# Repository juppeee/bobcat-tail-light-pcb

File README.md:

# Tail Light PCB for the AN3DRC Skid Steer Loader

PCB for working tail, brake and reverse lights in the tailgate of the
AN3DRC 3D-printed RC Tracked Skid Steer Loader.

> **The skid steer loader is not my design.** The original model, including the tailgate and
> the light module sketch, is by **Andrew (AN3DRC)**. You need his model to build this:
> **[buy it on Cults3D](https://cults3d.com/de/modell-3d/spiel/3d-printed-rc-tracked-skid-steer-loader-in-1-8-5-scale-by-an3drc-an3drc_construction)**.
> This repo only adds the tail light PCB.

> [!TIP]
> **Where to get the board:** I ordered mine from **[JLCPCB](https://jlcpcb.com)**. It worked
> very well and wasn't expensive. Upload the Gerber ZIP from the
> [release](../../releases/latest) and keep the default settings, that's it.
> Any other PCB maker works too, see [How to order](#how-to-order).

**Print files (tailgate frame, bezel, LED housings, lenses) and assembly: [MakerWorld](https://makerworld.com/de/collections/37654355-bobcat-an3drc-skid-steer)**

**[View the assembled PCB in 3D](3D/Tail_Light_PCB_THT.stl)** (GitHub shows an interactive viewer: rotate, zoom)

Board: 134 × 30 mm, 2 layers, 1.6 mm. 8 LEDs (3 mm) on the front facing the tailgate, all
other parts on the back. 4 mounting holes 2.2 mm (M2 or 2.2 mm self-tapping screws, max. 5 mm long).
Driven by a Pro Micro: 4 channels, each pin HIGH switches its two LEDs on through a low-side
MOSFET. The LEDs run from the 12 V battery (3S LiPo).

## Download

Ready-to-upload Gerber ZIPs are attached to the [latest release](../../releases/latest).

## How to order

Any PCB maker works (JLCPCB, PCBWay, Aisler, Elecrow, ...). Pick the one you like, prices
differ more by shipping than by the board.

**1. Board only (THT or SMD version)**
1. Download the Gerber ZIP of your version from the [release](../../releases/latest):
   `Heck_LED_THT_Gerber.zip` or `Heck_LED_SMD_Gerber.zip`.
2. Upload the ZIP **as it is**. Don't unpack it, the maker reads the outline, size and layers from it.
3. Settings: keep the defaults. If asked:

   | Option | Value |
   |---|---|
   | Layers | 2 |
   | Thickness | 1.6 mm |
   | Material | FR-4 |
   | Copper | 1 oz |
   | Surface finish | HASL (lead-free if you prefer), ENIG also fine |
   | Solder mask / silkscreen color | any |
   | Quantity | the minimum (usually 5), one board per tailgate |

   Some makers print an order number on the board. You can usually remove it for a small fee or leave it, it's on the back.
4. Solder the parts yourself (see [Parts per tailgate](#parts-per-tailgate) and `BOM.csv`).

**2. Board with SMD parts already assembled (SMD version only)**

Order like above, then switch on the maker's assembly service ("PCB Assembly", "SMT", ...) and upload two more files from `2_SMD_factory_assembled`:

| File | What the maker calls it |
|---|---|
| `JLCPCB_BOM.csv` | BOM / bill of materials. Columns: value, designators, footprint, LCSC part number |
| `JLCPCB_CPL.csv` (JLCPCB) or `pick_and_place_generic.csv` (others) | CPL / centroid / pick and place / position file |

- Assembly side: **Bottom**. All SMD parts sit on the back, the LEDs are on the front.
- In the preview, check that the four SOT-23 MOSFETs (Q1–Q4) sit with their three pins on the three pads. If they're rotated, turn them in the preview tool.
- The LCSC numbers match JLCPCB's parts library. With other makers, use them to look up the part (value + package is all that matters: 0603 resistors 1 %, 2N7002 in SOT-23).
- Afterwards you still solder the 8 LEDs and the 2 connectors by hand.

## Two versions, same circuit and outline

| Folder | Version |
|---|---|
| [`1_THT_hand_soldered`](1_THT_hand_soldered) | Through-hole, solder it yourself. Upload `Heck_LED_THT_Gerber.zip` unchanged to any PCB maker (JLCPCB, PCBWay, Aisler, ...), default settings: 2 layers, 1.6 mm. `BOM.csv` = parts list (BS170 in TO-92, 1/4 W resistors). |
| [`2_SMD_factory_assembled`](2_SMD_factory_assembled) | SMD parts on the back, assembled by JLCPCB. Upload `Heck_LED_SMD_Gerber.zip`, enable "PCB Assembly", assembly side **Bottom**, upload `JLCPCB_BOM.csv` and `JLCPCB_CPL.csv` (all parts are basic parts with LCSC numbers). Check the SOT-23 rotation in the preview. `pick_and_place_generic.csv` is for other assembly services. You still hand-solder the 8 LEDs and the 2 connectors. |
| [`3_KiCad_source`](3_KiCad_source) | KiCad 10 projects of both versions. |

`Schematic.pdf` is drawn for the THT version. The SMD version is identical except BS170 → 2N7002 and SMD resistors.

## Channels (left + right side each)

| Channel | Position | Function | LED | Resistor |
|---|---|---|---|---|
| K1 | outer top | tail light | red | 1.5 k |
| K2 | outer bottom | tail light | red | 1.5 k |
| K3 | inner top | brake light | red | 680 |
| K4 | inner bottom | reverse light | white | 1 k |

R9–R12 = gate resistors (1 k), R13–R16 = 100 k pulldowns.

## Connectors

Straight magnetic pogo connectors, 2.5 mm pitch, 0.7 mm pins (e.g. AliExpress "5Pin 2.5mm" / "2Pin 2.5mm").
No 90° types, no 2.8 mm pitch.

- **J1** (5 pins, "PRO MICRO"): GND, K1, K2, K3, K4 (5 V signals)
- **J2** (2 pins, "AKKU 12V"): pin 1 = +, pin 2 = −

Battery minus and Pro Micro GND must be connected.

LED marking: `+` = anode (outer, long leg), `−` = cathode (inner, square pad, flat side).

## Works with the original AN3DRC light module sketch

No extra firmware needed. The board expects one 5 V signal per channel (HIGH = on), which is
exactly what the original AN3DRC sketch outputs:

| Original sketch | Pro Micro pin | PCB |
|---|---|---|
| `light` (light switch channel) | A0 (18) | K1 + K2 (tail lights) |
| `rev1` (both tracks reversing) | 4 | K4 (reverse lights) |
| – | GND | GND |

The original sketch has no brake light. Either leave K3 unconnected, or put it on A0 as well
so the inner red LEDs glow as tail lights too.

**Take the signal directly from the Pro Micro pin**, not from the lamp outputs of the original
light module: those are switched to ground and carry 12 V.

## Parts per tailgate

| Part | Qty |
|---|---|
| LED 3 mm red, high brightness | 6 |
| LED 3 mm white, high brightness | 2 |
| Magnetic pogo connector 5-pin + 2-pin, straight, 2.5 mm | 1 set each |
| Screws M2 × 5 or 2.2 × 4.5 self-tapping | 4 |
| THT only: BS170 (TO-92, **not** 2N7000) | 4 |
| THT only: resistors 1/4 W: 1.5 k ×4, 680 ×2, 1 k ×6, 100 k ×4 | |

DRC: 0 unconnected pads. The remaining warnings are silkscreen overlaps only.

## Questions & help

Stuck somewhere or found a problem? Leave a comment on
[MakerWorld](https://makerworld.com/de/collections/37654355-bobcat-an3drc-skid-steer) or open an
[issue](../../issues) here, and I'll get back to you when I can.

## License

PCB design: [CC BY-NC 4.0](LICENSE). Build it, modify it and share it, as long as you credit
juppeee. **No commercial use**: don't sell boards, kits or assembled parts.

The skid steer loader itself, its tailgate and the light module sketch belong to AN3DRC and
are not covered by this license.

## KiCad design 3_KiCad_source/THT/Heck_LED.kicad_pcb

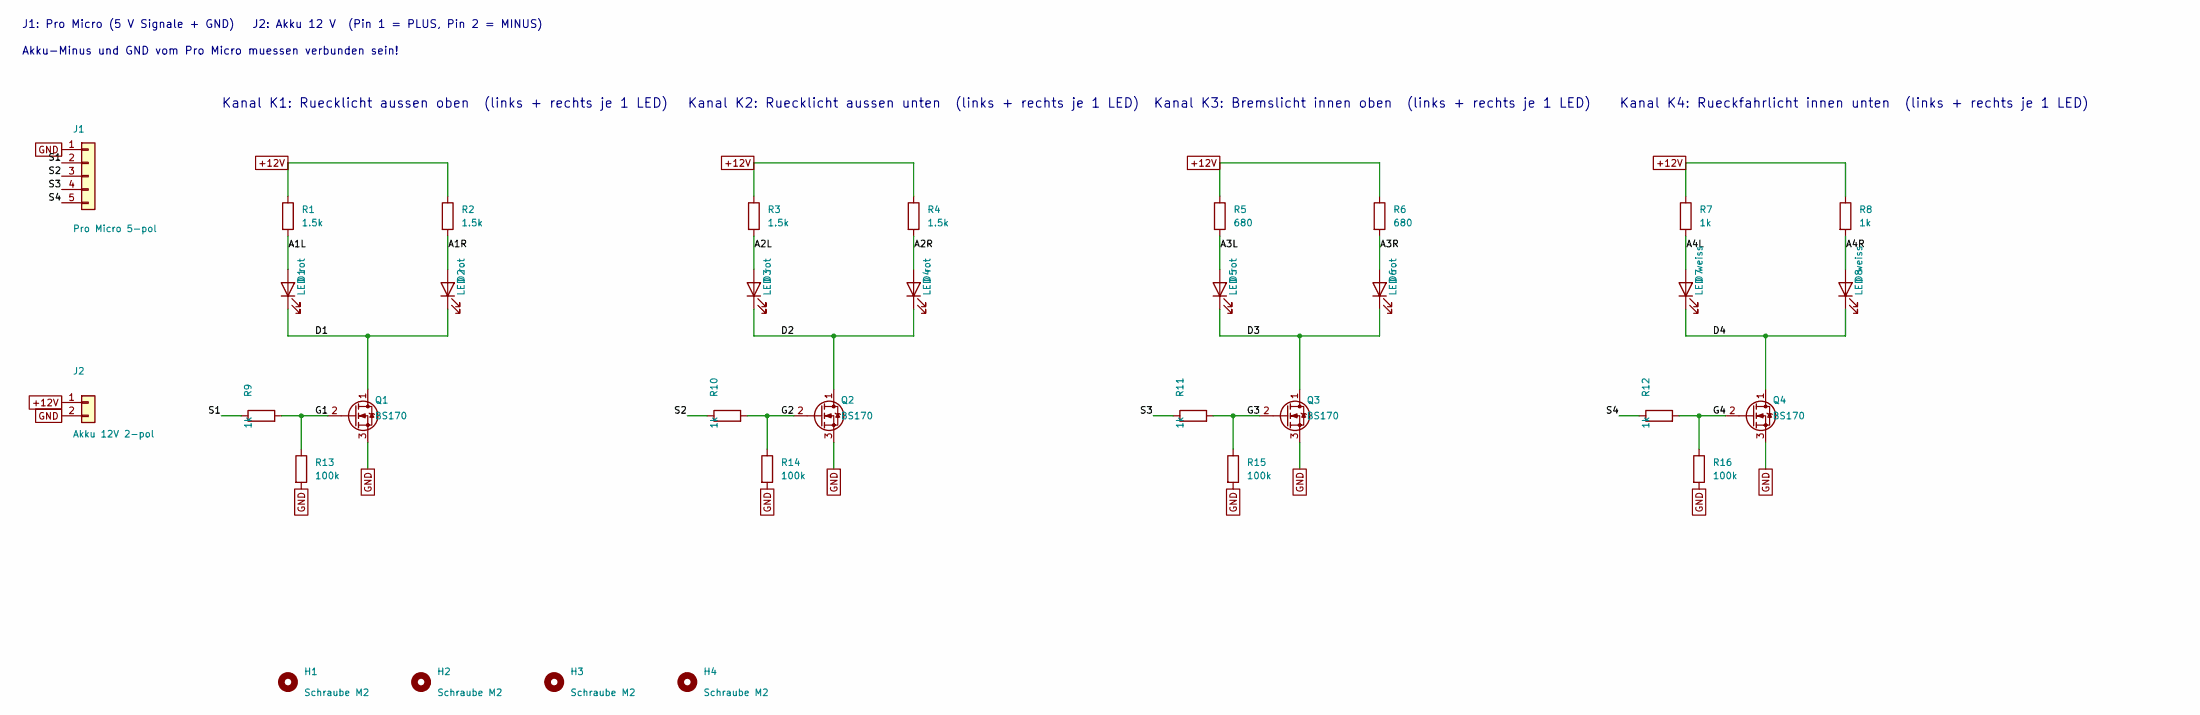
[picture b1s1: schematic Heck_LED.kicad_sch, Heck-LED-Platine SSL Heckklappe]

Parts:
D1, D2, D3, D4, D5, D6: LED rot; LED_D3.0mm
D7, D8: LED weiss; LED_D3.0mm
H1, H2, H3, H4: Schraube M2; MountingHole_2.2mm_M2
J1: Pro Micro 5-pol; MagPogo_1x05_P2.50mm_Straight
J2: Akku 12V 2-pol; MagPogo_1x02_P2.50mm_Straight
Q1, Q2, Q3, Q4: BS170; TO-92_Inline_Wide
R1, R2, R3, R4: 1.5k; R_Axial_DIN0207_L6.3mm_D2.5mm_P7.62mm_Horizontal
R5, R6: 680; R_Axial_DIN0207_L6.3mm_D2.5mm_P7.62mm_Horizontal
R7, R8, R9, R10, R11, R12: 1k; R_Axial_DIN0207_L6.3mm_D2.5mm_P7.62mm_Horizontal
R13, R14, R15, R16: 100k; R_Axial_DIN0207_L6.3mm_D2.5mm_P7.62mm_Horizontal

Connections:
+12V: J2.1, R1.1, R2.1, R3.1, R4.1, R5.1, R6.1, R7.1, R8.1
/A1L: D1.2 (A), R1.2
/A1R: D2.2 (A), R2.2
/A2L: D3.2 (A), R3.2
/A2R: D4.2 (A), R4.2
/A3L: D5.2 (A), R5.2
/A3R: D6.2 (A), R6.2
/A4L: D7.2 (A), R7.2
/A4R: D8.2 (A), R8.2
/D1: D1.1 (K), D2.1 (K), Q1.1 (D)
/D2: D3.1 (K), D4.1 (K), Q2.1 (D)
/D3: D5.1 (K), D6.1 (K), Q3.1 (D)
/D4: D7.1 (K), D8.1 (K), Q4.1 (D)
/G1: Q1.2 (G), R9.2, R13.1
/G2: Q2.2 (G), R10.2, R14.1
/G3: Q3.2 (G), R11.2, R15.1
/G4: Q4.2 (G), R12.2, R16.1
/S1: J1.2, R9.1
/S2: J1.3, R10.1
/S3: J1.4, R11.1
/S4: J1.5, R12.1
GND: J1.1, J2.2, Q1.3 (S), Q2.3 (S), Q3.3 (S), Q4.3 (S), R13.2, R14.2, R15.2, R16.2

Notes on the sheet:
Kanal K1: Ruecklicht aussen oben (links + rechts je 1 LED)
Kanal K2: Ruecklicht aussen unten (links + rechts je 1 LED)
Kanal K3: Bremslicht innen oben (links + rechts je 1 LED)
Kanal K4: Rueckfahrlicht innen unten (links + rechts je 1 LED)
J1: Pro Micro (5 V Signale + GND) J2: Akku 12 V (Pin 1 = PLUS, Pin 2 = MINUS)
Akku-Minus und GND vom Pro Micro muessen verbunden sein!

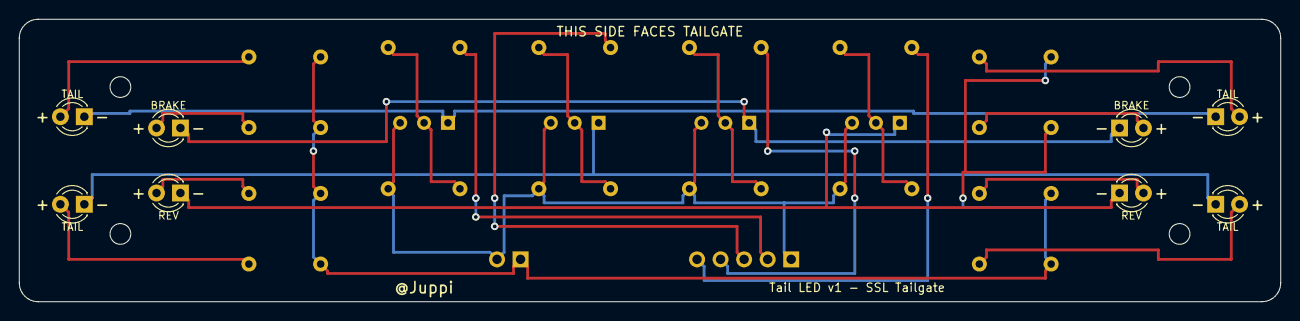
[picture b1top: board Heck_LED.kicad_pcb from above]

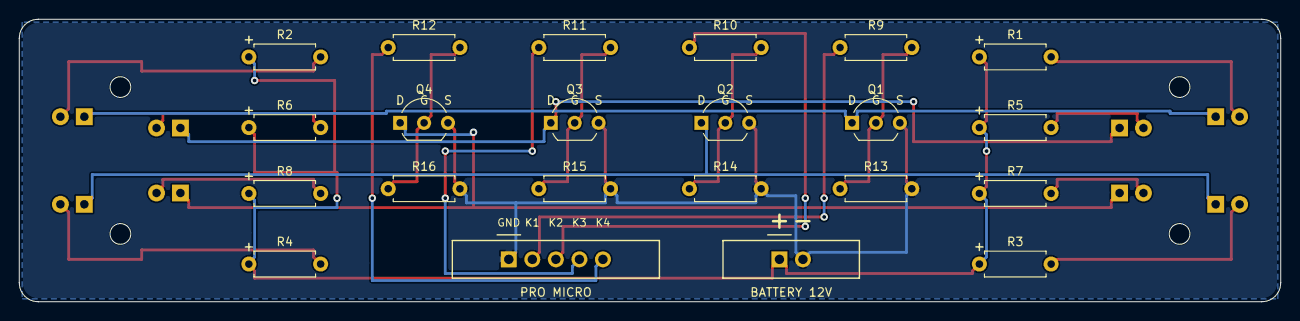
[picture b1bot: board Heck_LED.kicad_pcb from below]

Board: 2 copper layers, 134.0 x 30.0 mm, 34 parts (22 on the bottom side), 22 nets.

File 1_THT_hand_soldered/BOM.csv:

"Reference","Value","Footprint"
"D1-D6","LED rot","LED_THT:LED_D3.0mm"
"D7,D8","LED weiss","LED_THT:LED_D3.0mm"
"J1","Pro Micro 5-pol","Heck_LED:MagPogo_1x05_P2.50mm_Straight"
"J2","Akku 12V 2-pol","Heck_LED:MagPogo_1x02_P2.50mm_Straight"
"Q1-Q4","BS170","Package_TO_SOT_THT:TO-92_Inline_Wide"
"R1-R4","1.5k","Resistor_THT:R_Axial_DIN0207_L6.3mm_D2.5mm_P7.62mm_Horizontal"
"R5,R6","680","Resistor_THT:R_Axial_DIN0207_L6.3mm_D2.5mm_P7.62mm_Horizontal"
"R7-R12","1k","Resistor_THT:R_Axial_DIN0207_L6.3mm_D2.5mm_P7.62mm_Horizontal"
"R13-R16","100k","Resistor_THT:R_Axial_DIN0207_L6.3mm_D2.5mm_P7.62mm_Horizontal"
